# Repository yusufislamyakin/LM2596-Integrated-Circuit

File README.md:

# LM2596 5V Buck Converter PCB

## Overview
- This project is a DC-DC buck converter designed using the LM2596.
- It steps down a 12V input voltage to a regulated 5V output.
- The circuit is designed and implemented in KiCad, including both schematic and PCB layout.
- Designed and implemented in KiCad
- Includes schematic, PCB layout, and production files

## Working Principle
The LM2596 operates as a switching regulator.
It rapidly switches the internal transistor on and off, transferring energy through the inductor.

-When the switch is ON, energy is stored in the inductor.
-When the switch is OFF, the stored energy is delivered to the load through the diode.
-The output voltage is regulated using a feedback network (R1 and R2).

## Components
- LM2596 switching regulator
- Schottky diode
- 33µH power inductor
- Input capacitor
- Output capacitor (low ESR)
- Feedback resistors (R1, R2)
- Compensation capacitor (CFF)
- Input and output connectors

## Images

### Schematic

### PCB Layout

### 3D View

## Design Notes
- Power traces are widened to handle higher current.
- A ground plane is used to improve stability and reduce noise.
- The switching node (L1–D1 connection) is kept as small as possible.
- Output capacitor is placed close to the inductor.
- Feedback path is kept short and away from noisy areas.
- PCB layout is optimized to minimize switching noise and improve efficiency

## Tools Used
- KiCad
- KiCad PCB Editor
- KiCad 3D Viewer

## Project Files

You can find the complete KiCad project files in the `kicad` folder, including schematic and PCB layout.

## Production Files

[Download Gerber Files](https://github.com/yusufislamyakin/LM2596-Integrated-Circuit/raw/main/gerber/gerber.zip)

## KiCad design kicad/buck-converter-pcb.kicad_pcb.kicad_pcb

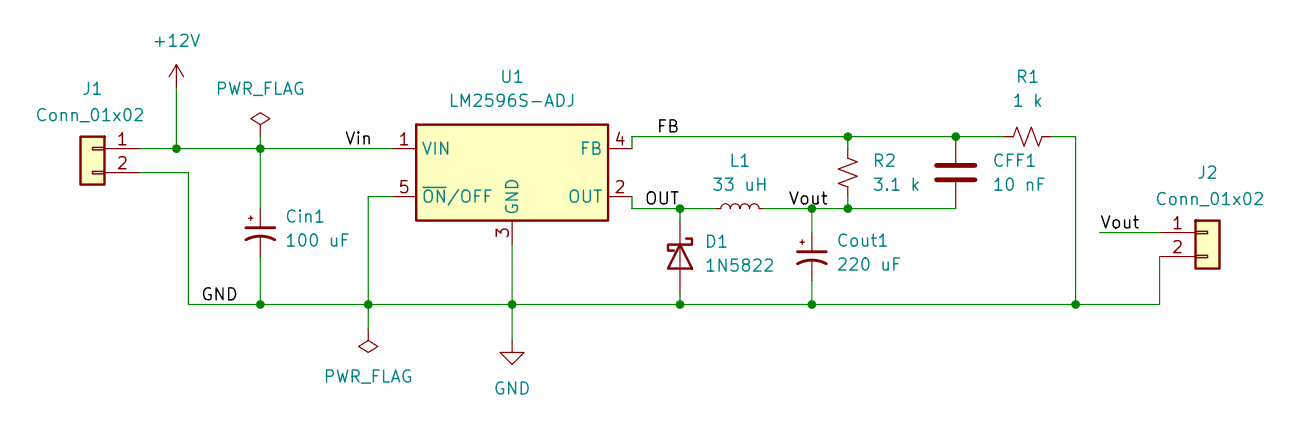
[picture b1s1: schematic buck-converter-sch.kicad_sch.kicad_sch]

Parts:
CFF1: 10 nF; C_0805_2012Metric_Pad1.18x1.45mm_HandSolder
Cin1: 100 uF; CP_Radial_D8.0mm_P5.00mm
Cout1: 220 uF; CP_Elec_10x10
D1: 1N5822; D_DO-201AD_P15.24mm_Horizontal
J1, J2: Conn_01x02; TerminalBlock_Phoenix_MKDS-1,5-2-5.08_1x02_P5.08mm_Horizont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
L1: 33 uH; DO5040H333MLD
R1: 1 k; R_0805_2012Metric_Pad1.20x1.40mm_HandSolder
R2: 3.1 k; R_0805_2012Metric_Pad1.20x1.40mm_HandSolder
U1: LM2596S-ADJ; TO-263-5_TabPin3

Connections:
+12V: Cin1.1, J1.1, U1.1 (VIN)
/FB: CFF1.1, R1.1, R2.2, U1.4 (FB)
/OUT: D1.1 (K), L1.1, U1.2 (OUT)
/Vout: CFF1.2, Cout1.1, J2.1, L1.2, R2.1
GND: Cin1.2, Cout1.2, D1.2 (A), J1.2, J2.2, R1.2, U1.3 (GND), U1.5 (~ON/OFF)

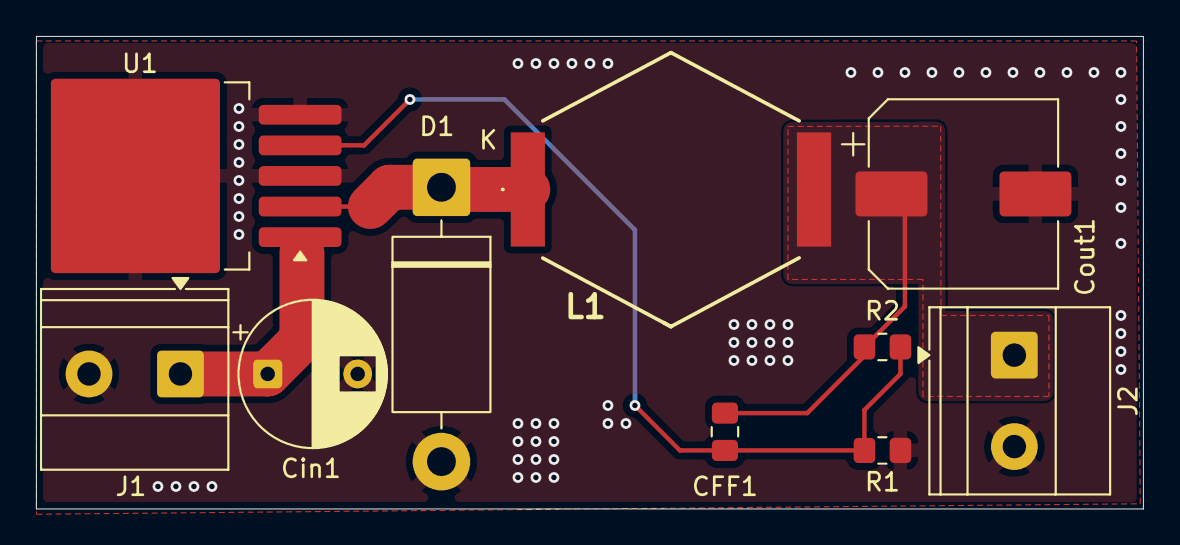
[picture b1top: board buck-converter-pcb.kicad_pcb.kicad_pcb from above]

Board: 2 copper layers, 61.5 x 26.2 mm, 10 parts (0 on the bottom side), 5 nets.
